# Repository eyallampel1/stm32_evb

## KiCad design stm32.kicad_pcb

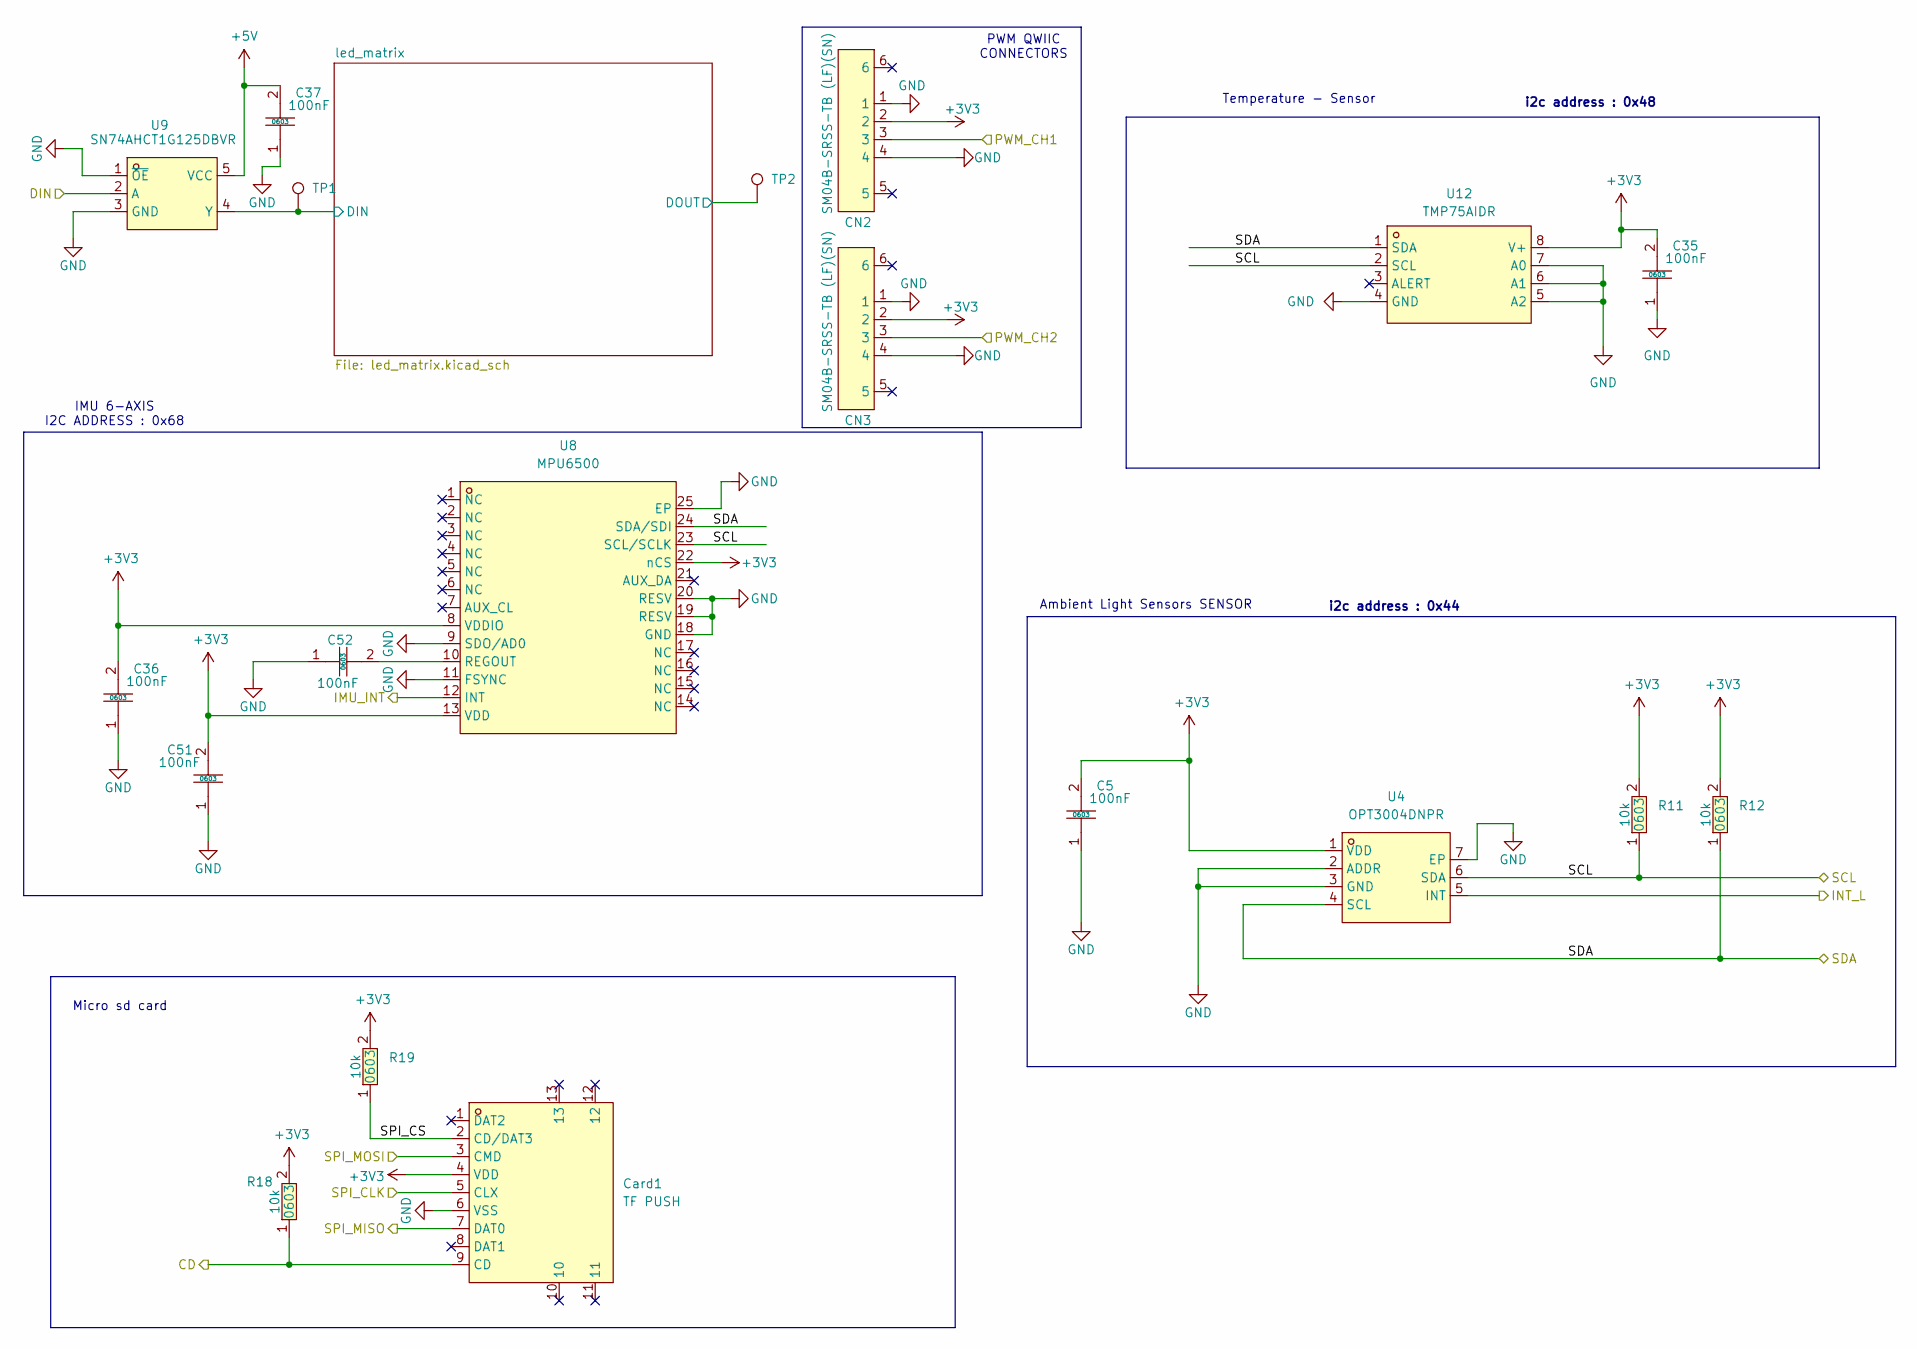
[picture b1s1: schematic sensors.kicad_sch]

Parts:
C5, C35, C36, C37, C51, C52: CC0603KRX7R9BB104; C0603; LCSC Part C14663
CN2, CN3: SM04B-SRSS-TB (LF)(SN); CONN-SMD_4P-P1.00_SM04B-SRSS-TB-LF-SN; LCSC Part C160404
Card1: TF PUSH; TF-SMD_TF-PUSH; LCSC Part C393941
R11, R12, R18, R19: 0603WAF1002T5E; R0603; LCSC Part C25804
TP1, TP2: TestPoint; TestPoint_Pad_2.0x2.0mm
U4: OPT3004DNPR; WSON-6_L2.0-W2.0-P0.65-TL-EP; LCSC Part C2655153
U8: MPU6500; QFN-24_L3.0-W3.0-P0.40-BL-EP; LCSC Part C50278
U9: SN74AHCT1G125DBVR; SOT-23-5_L3.0-W1.7-P0.95-LS2.8-BR; LCSC Part C7484
U12: TMP75AIDR; SOIC-8_L4.9-W3.9-P1.27-LS6.0-BL; LCSC Part C30389

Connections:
+3V3: C5.2, C35.2, C36.2, C51.2, CN2.2, CN3.2, Card1.4 (VDD), R11.2, R12.2, R18.2, R19.2, U4.1 (VDD), U8.8 (VDDIO), U8.13 (VDD), U8.22 (nCS), U12.8 (V+); also elsewhere on the board
+5V: C37.2, U9.5 (VCC); also elsewhere on the board
/sensors/SCL: R11.1, U4.6 (SDA), U8.23 (SCL/SCLK), U12.2 (SCL); also elsewhere on the board
/sensors/SDA: R12.1, U4.4 (SCL), U8.24 (SDA/SDI), U12.1 (SDA); also elsewhere on the board
/sensors/SPI_CS: Card1.2 (CD/DAT3), R19.1
/sensors/led_matrix/DIN: TP1.1, U9.4 (Y); also elsewhere on the board
/sensors/led_matrix/DOUT: TP2.1; also elsewhere on the board
/stm32_page/IMU_INT: U8.12 (INT); also elsewhere on the board
/stm32_page/PWM_CH1: CN2.3; also elsewhere on the board
/stm32_page/PWM_CH4: CN3.3; also elsewhere on the board
/stm32_page/RGB_LEDS: U9.2 (A); also elsewhere on the board
/stm32_page/SD_CD: Card1.9 (CD), R18.1; also elsewhere on the board
/stm32_page/SPI1_MISO: Card1.7 (DAT0); also elsewhere on the board
/stm32_page/SPI1_MOSI: Card1.3 (CMD); also elsewhere on the board
/stm32_page/SPI1_SCK: Card1.5 (CLX); also elsewhere on the board
/stm32_page/SYS_WKUP1: U4.5 (INT); also elsewhere on the board
GND: C5.1, C35.1, C36.1, C37.1, C51.1, C52.1, CN2.1, CN2.4, CN3.1, CN3.4, Card1.6 (VSS), U4.2 (ADDR), U4.3 (GND), U4.7 (EP), U8.9 (SDO/AD0), U8.11 (FSYNC), U8.18 (GND), U8.19 (RESV), U8.20 (RESV), U8.25 (EP), U9.1 (~OE), U9.3 (GND), U12.4 (GND), U12.5 (A2), U12.6 (A1), U12.7 (A0); also elsewhere on the board
unnamed: C52.2, U8.10 (REGOUT)

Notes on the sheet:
PWM QWIIC CONNECTORS
Temperature - Sensor
i2c address : 0x48
Ambient Light Sensors SENSOR
IMU 6-AXIS I2C ADDRESS : 0x68
i2c address : 0x44
Micro sd card

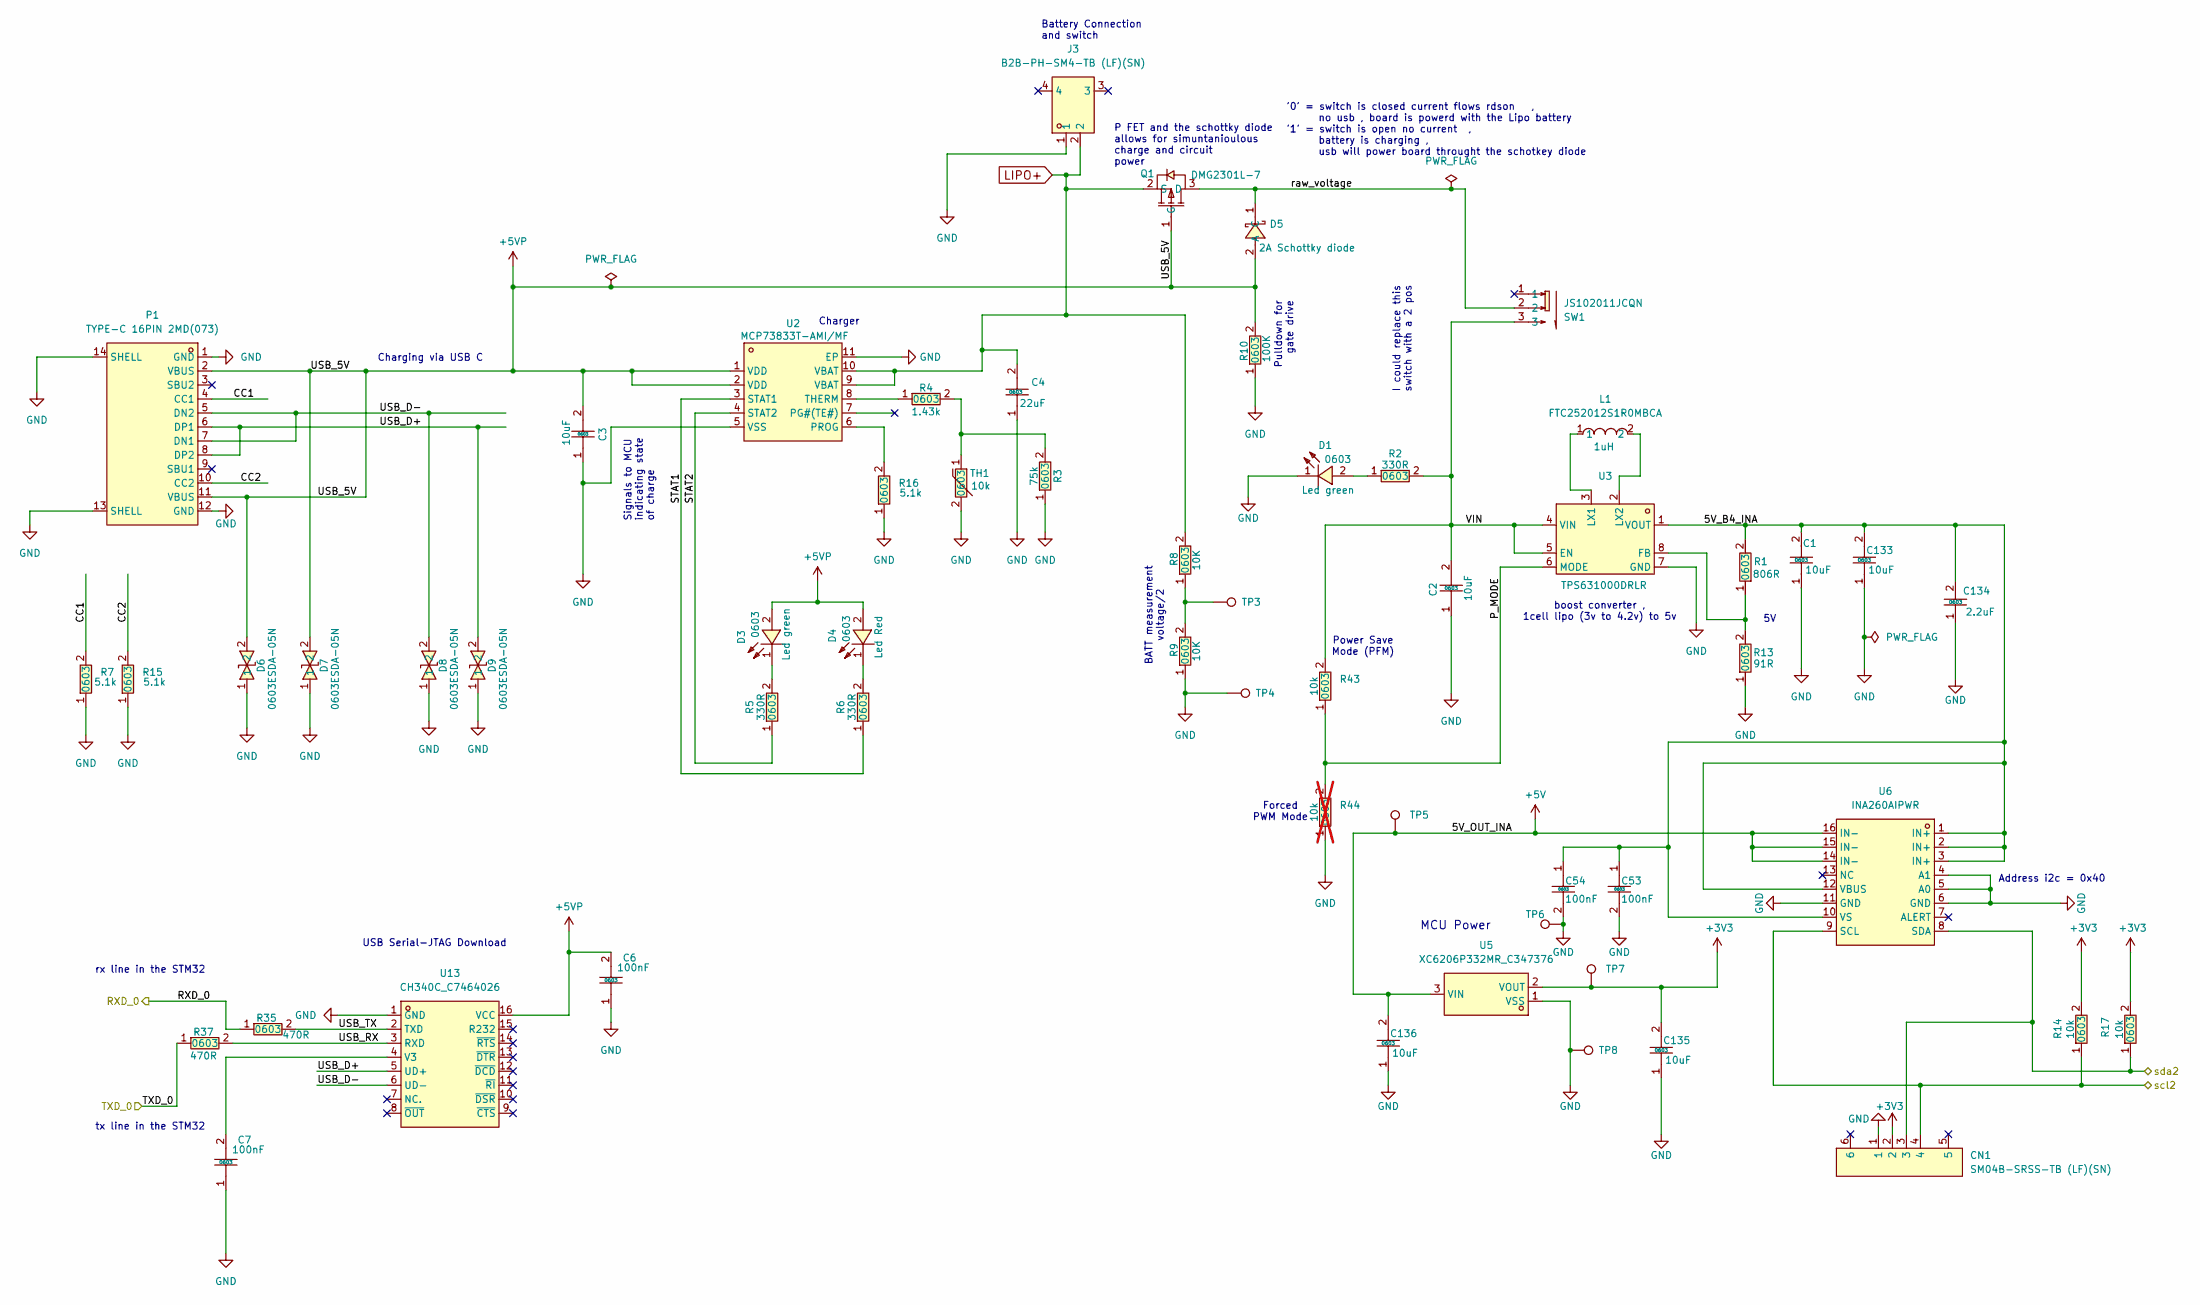
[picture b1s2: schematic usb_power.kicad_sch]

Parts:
C1, C2, C3, C133, C135, C136: CL10A106KP8NNNC; C0603; LCSC Part C19702
C4: CL10A226MP8NUNE; C0603; LCSC Part C86295
C6, C7, C53, C54: CC0603KRX7R9BB104; C0603; LCSC Part C14663
C134: CL10A225KO8NNNC; C0603; LCSC Part C23630
CN1: SM04B-SRSS-TB (LF)(SN); CONN-SMD_4P-P1.00_SM04B-SRSS-TB-LF-SN; LCSC Part C160404
D1, D3: 0603 Green 509-620mcd; LED0603-RD; LCSC Part C12624
D4: KT-0603R; LED0603-RD; LCSC Part C2286
D5: MBRA210LT3G_C5337989; SMA_L4.3-W2.6-LS5.1-RD; LCSC Part C5337989
D6, D7, D8, D9: 0603ESDA-05N; D0603-BI; LCSC Part C316054
J3: B2B-PH-SM4-TB (LF)(SN); CONN-SMD_B2B-PH-SM4-TB-LF-SN; LCSC Part C265003
L1: FTC252012S1R0MBCA; IND-SMD_L2.5-W2.0-VLS252012CX-150M; LCSC Part C5832370
P1: TYPE-C 16PIN 2MD(073); USB-C-SMD_TYPE-C-6PIN-2MD-073; LCSC Part C2765186
Q1: DMG2301L-7; SOT-23-3_L2.9-W1.3-P1.90-LS2.4-BR; LCSC Part C102619
R1: 0603WAF8060T5E; R0603; LCSC Part C23116
R2, R5, R6: 0603WAF3300T5E; R0603; LCSC Part C23138
R3: 0603WAF7502T5E; R0603; LCSC Part C23242
R4: 0603WAF1431T5E; R0603; LCSC Part C22840
R7, R15, R16: 0603WAF5101T5E; R0603; LCSC Part C23186
R8, R9, R14, R17, R43: 0603WAF1002T5E; R0603; LCSC Part C25804
R10: 0603WAF1003T5E; R0603; LCSC Part C25803
R13: 0603WAF910JT5E; R0603; LCSC Part C351621
R35, R37: 0603WAF4700T5E; R0603; LCSC Part C23179
R44: 0603WAF1002T5E; R0603; LCSC Part C25804; not fitted
SW1: JS102011JCQN; SW-SMD_JS102011JCQN; LCSC Part C221659
TH1: NCP18XH103F03RB; R0603; LCSC Part C13564
TP3, TP4, TP5, TP6, TP7, TP8: TestPoint; TestPoint_Pad_2.0x2.0mm
U2: MCP73833T-AMI/MF; DFN-10_L3.0-W3.0-P0.50-BL-EP-1; LCSC Part C340160
U3: TPS631000DRLR; SOT-583-8_L2.1-W1.2-P0.50-LS1.6-BL; LCSC Part C5219190
U5: XC6206P332MR_C347376; SOT-23-3_L3.0-W1.7-P0.95-LS2.9-BR; LCSC Part C347376
U6: INA260AIPWR; TSSOP-16_L5.0-W4.4-P0.65-LS6.4-BL-1; LCSC Part C2155885
U13: CH340C_C7464026; SOP-16_L10.0-W3.9-P1.27-LS6.0-BL; LCSC Part C7464026

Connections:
+3V3: C135.2, CN1.2, R14.2, R17.2, TP7.1, U5.2 (VOUT); also elsewhere on the board
+5V: C136.2, TP5.1, U5.3 (VIN), U6.14 (IN-), U6.15 (IN-), U6.16 (IN-); also elsewhere on the board
+5VP: C3.2, C6.2, D3.2 (A), D4.2 (A), D5.2 (A), D6.2, D7.2, P1.2 (VBUS), P1.11 (VBUS), Q1.1 (G), R10.2, U2.1 (VDD), U2.2 (VDD), U13.16 (VCC)
/USB/5V_B4_INA: C1.2, C53.1, C54.1, C133.2, C134.2, R1.2, U3.1 (VOUT), U6.1 (IN+), U6.2 (IN+), U6.3 (IN+), U6.10 (VS), U6.12 (VBUS)
/USB/CC1: P1.4 (CC1), R7.2
/USB/CC2: P1.10 (CC2), R15.2
/USB/P_MODE: R43.1, R44.2, U3.6 (MODE)
/USB/RXD_0: R35.1; also elsewhere on the board
/USB/STAT1: R6.1, U2.3 (STAT1)
/USB/STAT2: R5.1, U2.4 (STAT2)
/USB/TXD_0: R37.1; also elsewhere on the board
/USB/USB_D+: D9.2, P1.6 (DP1), P1.8 (DP2), U13.5 (UD+)
/USB/USB_D-: D8.2, P1.5 (DN2), P1.7 (DN1), U13.6 (UD-)
/USB/USB_RX: R37.2, U13.3 (RXD)
/USB/USB_TX: R35.2, U13.2 (TXD)
/USB/VIN: C2.2, R2.2, R43.2, SW1.3, U3.4 (VIN), U3.5 (EN)
/USB/raw_voltage: D5.1 (C), Q1.3 (D), SW1.2
/stm32_page/I2C3_SCL: CN1.4, R14.1, U6.9 (SCL); also elsewhere on the board
/stm32_page/I2C3_SDA: CN1.3, R17.1, U6.8 (SDA); also elsewhere on the board
GND: C1.1, C2.1, C3.1, C4.1, C6.1, C7.1, C53.2, C54.2, C133.1, C134.1, C135.1, C136.1, CN1.1, D1.1 (K), D6.1, D7.1, D8.1, D9.1, J3.1, P1.1 (GND), P1.12 (GND), P1.13 (SHELL), P1.14 (SHELL), R3.1, R7.1, R9.1, R10.1, R13.1, R15.1, R16.1, R44.1, TH1.2, TP4.1, TP6.1, TP8.1, U2.5 (VSS), U2.11 (EP), U3.7 (GND), U5.1 (VSS), U6.4 (A1), U6.5 (A0), U6.6 (GND), U6.11 (GND), U13.1 (GND); also elsewhere on the board
LIPO+: C4.2, J3.2, Q1.2 (S), R8.2, U2.9 (VBAT), U2.10 (VBAT)
unnamed: D1.2 (A), R2.1
unnamed: D3.1 (K), R5.2
unnamed: D4.1 (K), R6.2
unnamed: R3.2, R4.2, TH1.1
unnamed: R8.1, R9.2, TP3.1
unnamed: R16.2, U2.6 (PROG)
unnamed: R4.1, U2.8 (THERM)
unnamed: R1.1, R13.2, U3.8 (FB)
unnamed: L1.1, U3.3 (LX1)
unnamed: L1.2, U3.2 (LX2)
unnamed: C7.2, U13.4 (V3)

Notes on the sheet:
Charger
Forced PWM Mode
rx line in the STM32
P FET and the schottky diode allows for simuntanioulous charge and circuit power
Pulldown for gate drive
USB Serial-JTAG Download
'0' = switch is closed current flows rdson , no usb , board is powerd with the Lipo battery '1' = switch is open no current , battery is charging , usb will power board throught the schotkey diode
boost converter , 1cell lipo (3v to 4.2v) to 5v
BATT measurement voltage/2
Power Save Mode (PFM)
Battery Connection and switch
Address i2c = 0x40
tx line in the STM32
I could replace this switch with a 2 pos
Signals to MCU indicating state of charge
MCU Power
Charging via USB C

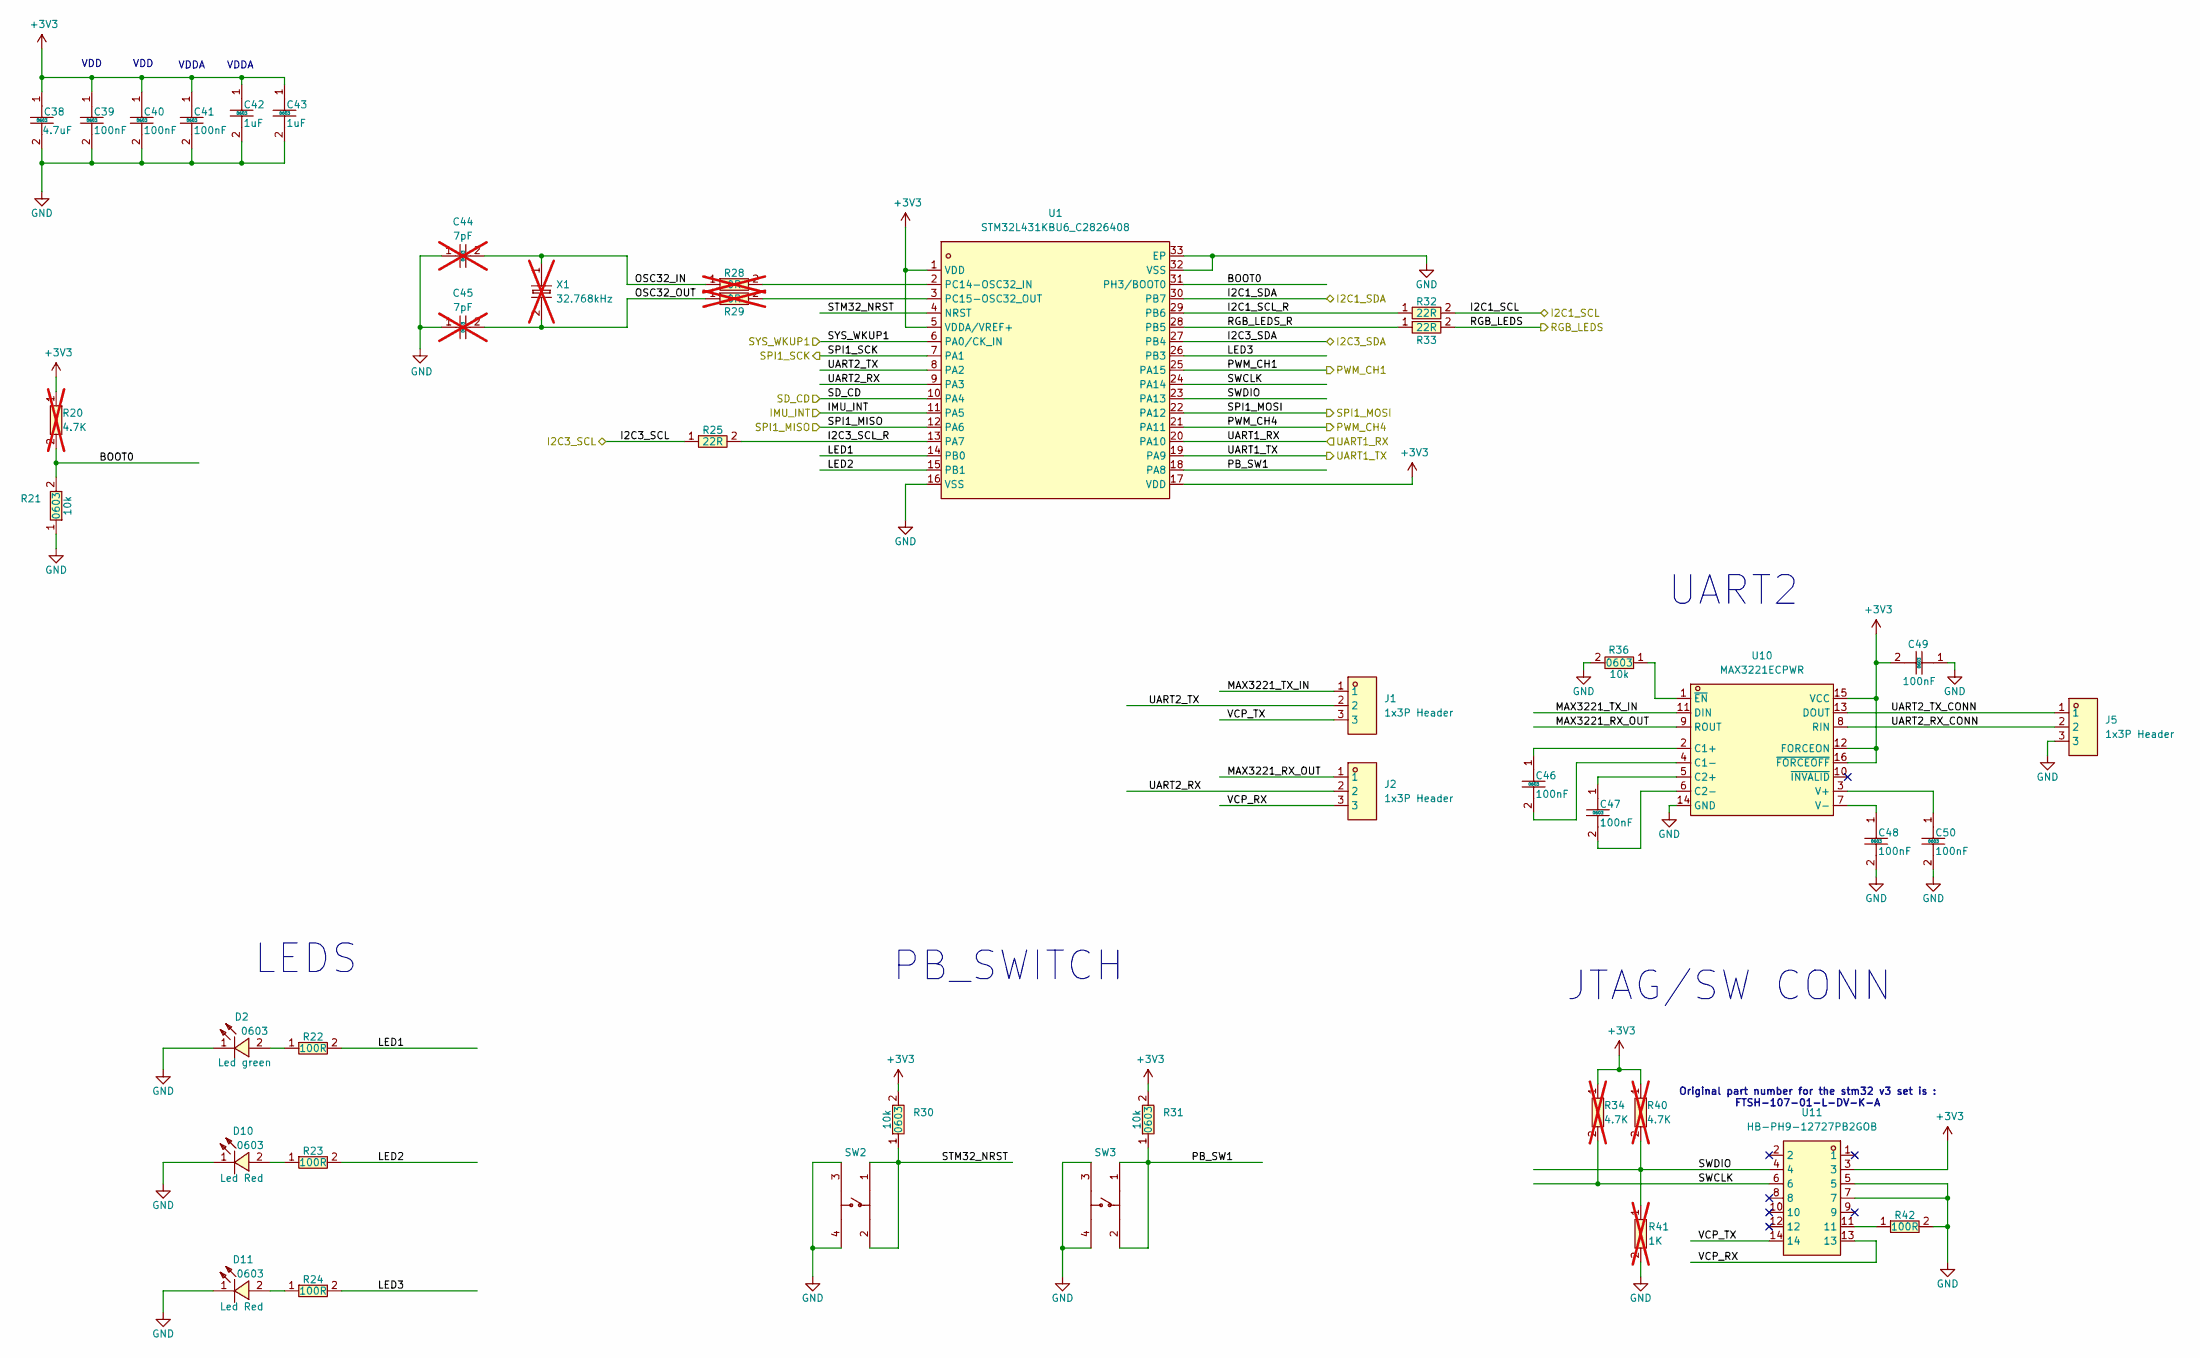
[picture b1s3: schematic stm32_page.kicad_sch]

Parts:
C38: CL10A475KO8NNNC; C0603; LCSC Part C19666
C39, C40, C41, C46, C47, C48, C49, C50: CC0603KRX7R9BB104; C0603; LCSC Part C14663
C42, C43: CL10A105KB8NNNC; C0603; LCSC Part C15849
C44, C45: 0603CG7R0C500NT; C0603; LCSC Part C1682; not fitted
D2: 0603 Green 509-620mcd; LED0603-RD; LCSC Part C12624
D10, D11: KT-0603R; LED0603-RD; LCSC Part C2286
J1, J2, J5: PZ254V-11-03P_C2937625; HDR-TH_3P-P2.54-V-M; LCSC Part C2937625
R20, R34, R40: 0603WAF4701T5E; R0603; LCSC Part C23162; not fitted
R21, R30, R31, R36: 0603WAF1002T5E; R0603; LCSC Part C25804
R22, R23, R24, R42: 0603WAF1000T5E; R0603; LCSC Part C22775
R25, R32, R33: 0603WAF220JT5E; R0603; LCSC Part C23345
R28, R29: 0603WAF0000T5E; R0603; LCSC Part C21189; not fitted
R41: 0603WAF1001T5E; R0603; LCSC Part C21190; not fitted
SW2, SW3: 6.0*6.0*6.0; SW-SMD_4P-L6.0-W6.0-P4.50-LS8.6; LCSC Part C5127964
U1: STM32L431KBU6_C2826408; QFN-32_L5.0-W5.0-P0.50-TL-EP3.5; LCSC Part C2826408
U10: MAX3221ECPWR; TSSOP-16_L5.0-W4.4-P0.65-LS6.4-BL; LCSC Part C350553
U11: HB-PH9-12727PB2GOB; HDR-SMD_14P-P1.27-V-M-R2-C7-LS5.5; LCSC Part C6332251
X1: SC-32S32.768kHz20PPM7pF; OSC-SMD_L3.2-W1.5; LCSC Part C97604; not fitted

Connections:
+3V3: C38.1, C39.1, C40.1, C41.1, C42.1, C43.1, C49.2, R20.1, R30.2, R31.2, R34.1, R40.1, U1.1 (VDD), U1.5 (VDDA/VREF+), U1.17 (VDD), U10.12 (FORCEON), U10.15 (VCC), U10.16 (~FORCEOFF), U11.3; also elsewhere on the board
/USB/RXD_0: U1.20 (PA10); also elsewhere on the board
/USB/TXD_0: U1.19 (PA9); also elsewhere on the board
/sensors/SCL: R32.2; also elsewhere on the board
/sensors/SDA: U1.30 (PB7); also elsewhere on the board
/stm32_page/BOOT0: R20.2, R21.2, U1.31 (PH3/BOOT0)
/stm32_page/I2C1_SCL_R: R32.1, U1.29 (PB6)
/stm32_page/I2C3_SCL: R25.1; also elsewhere on the board
/stm32_page/I2C3_SCL_R: R25.2, U1.13 (PA7)
/stm32_page/I2C3_SDA: U1.27 (PB4); also elsewhere on the board
/stm32_page/IMU_INT: U1.11 (PA5); also elsewhere on the board
/stm32_page/LED1: R22.2, U1.14 (PB0)
/stm32_page/LED2: R23.2, U1.15 (PB1)
/stm32_page/LED3: R24.2, U1.26 (PB3)
/stm32_page/MAX3221_RX_OUT: J2.1, U10.9 (ROUT)
/stm32_page/MAX3221_TX_IN: J1.1, U10.11 (DIN)
/stm32_page/OSC32_IN: C44.2, R28.1, X1.1
/stm32_page/OSC32_OUT: C45.2, R29.1, X1.2
/stm32_page/PB_SW1: R31.1, SW3.1, SW3.2, U1.18 (PA8)
/stm32_page/PWM_CH1: U1.25 (PA15); also elsewhere on the board
/stm32_page/PWM_CH4: U1.21 (PA11); also elsewhere on the board
/stm32_page/RGB_LEDS: R33.2; also elsewhere on the board
/stm32_page/RGB_LEDS_R: R33.1, U1.28 (PB5)
/stm32_page/SD_CD: U1.10 (PA4); also elsewhere on the board
/stm32_page/SPI1_MISO: U1.12 (PA6); also elsewhere on the board
/stm32_page/SPI1_MOSI: U1.22 (PA12); also elsewhere on the board
/stm32_page/SPI1_SCK: U1.7 (PA1); also elsewhere on the board
/stm32_page/STM32_NRST: R30.1, SW2.1, SW2.2, U1.4 (NRST)
/stm32_page/SWCLK: R34.2, U1.24 (PA14), U11.6
/stm32_page/SWDIO: R40.2, R41.1, U1.23 (PA13), U11.4
/stm32_page/SYS_WKUP1: U1.6 (PA0/CK_IN); also elsewhere on the board
/stm32_page/UART2_RX: J2.2, U1.9 (PA3)
/stm32_page/UART2_RX_CONN: J5.2, U10.8 (RIN)
/stm32_page/UART2_TX: J1.2, U1.8 (PA2)
/stm32_page/UART2_TX_CONN: J5.1, U10.13 (DOUT)
/stm32_page/VCP_RX: J2.3, U11.13
/stm32_page/VCP_TX: J1.3, U11.14
GND: C38.2, C39.2, C40.2, C41.2, C42.2, C43.2, C44.1, C45.1, C48.2, C49.1, C50.2, D2.1 (K), D10.1 (K), D11.1 (K), J5.3, R21.1, R36.2, R41.2, R42.2, SW2.3, SW2.4, SW3.3, SW3.4, U1.16 (VSS), U1.32 (VSS), U1.33 (EP), U10.14 (GND), U11.5, U11.7; also elsewhere on the board
unnamed: D2.2 (A), R22.1
unnamed: D10.2 (A), R23.1
unnamed: D11.2 (A), R24.1
unnamed: R42.1, U11.11
unnamed: R28.2, U1.2 (PC14-OSC32_IN)
unnamed: R29.2, U1.3 (PC15-OSC32_OUT)
unnamed: C46.1, U10.2 (C1+)
unnamed: C46.2, U10.4 (C1-)
unnamed: C47.1, U10.5 (C2+)
unnamed: C47.2, U10.6 (C2-)
unnamed: C50.1, U10.3 (V+)
unnamed: C48.1, U10.7 (V-)
unnamed: R36.1, U10.1 (~EN)

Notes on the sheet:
PB_SWITCH
LEDS
VDD
JTAG/SW CONN
VDDA
Original part number for the stm32 v3 set is : FTSH-107-01-L-DV-K-A
UART2

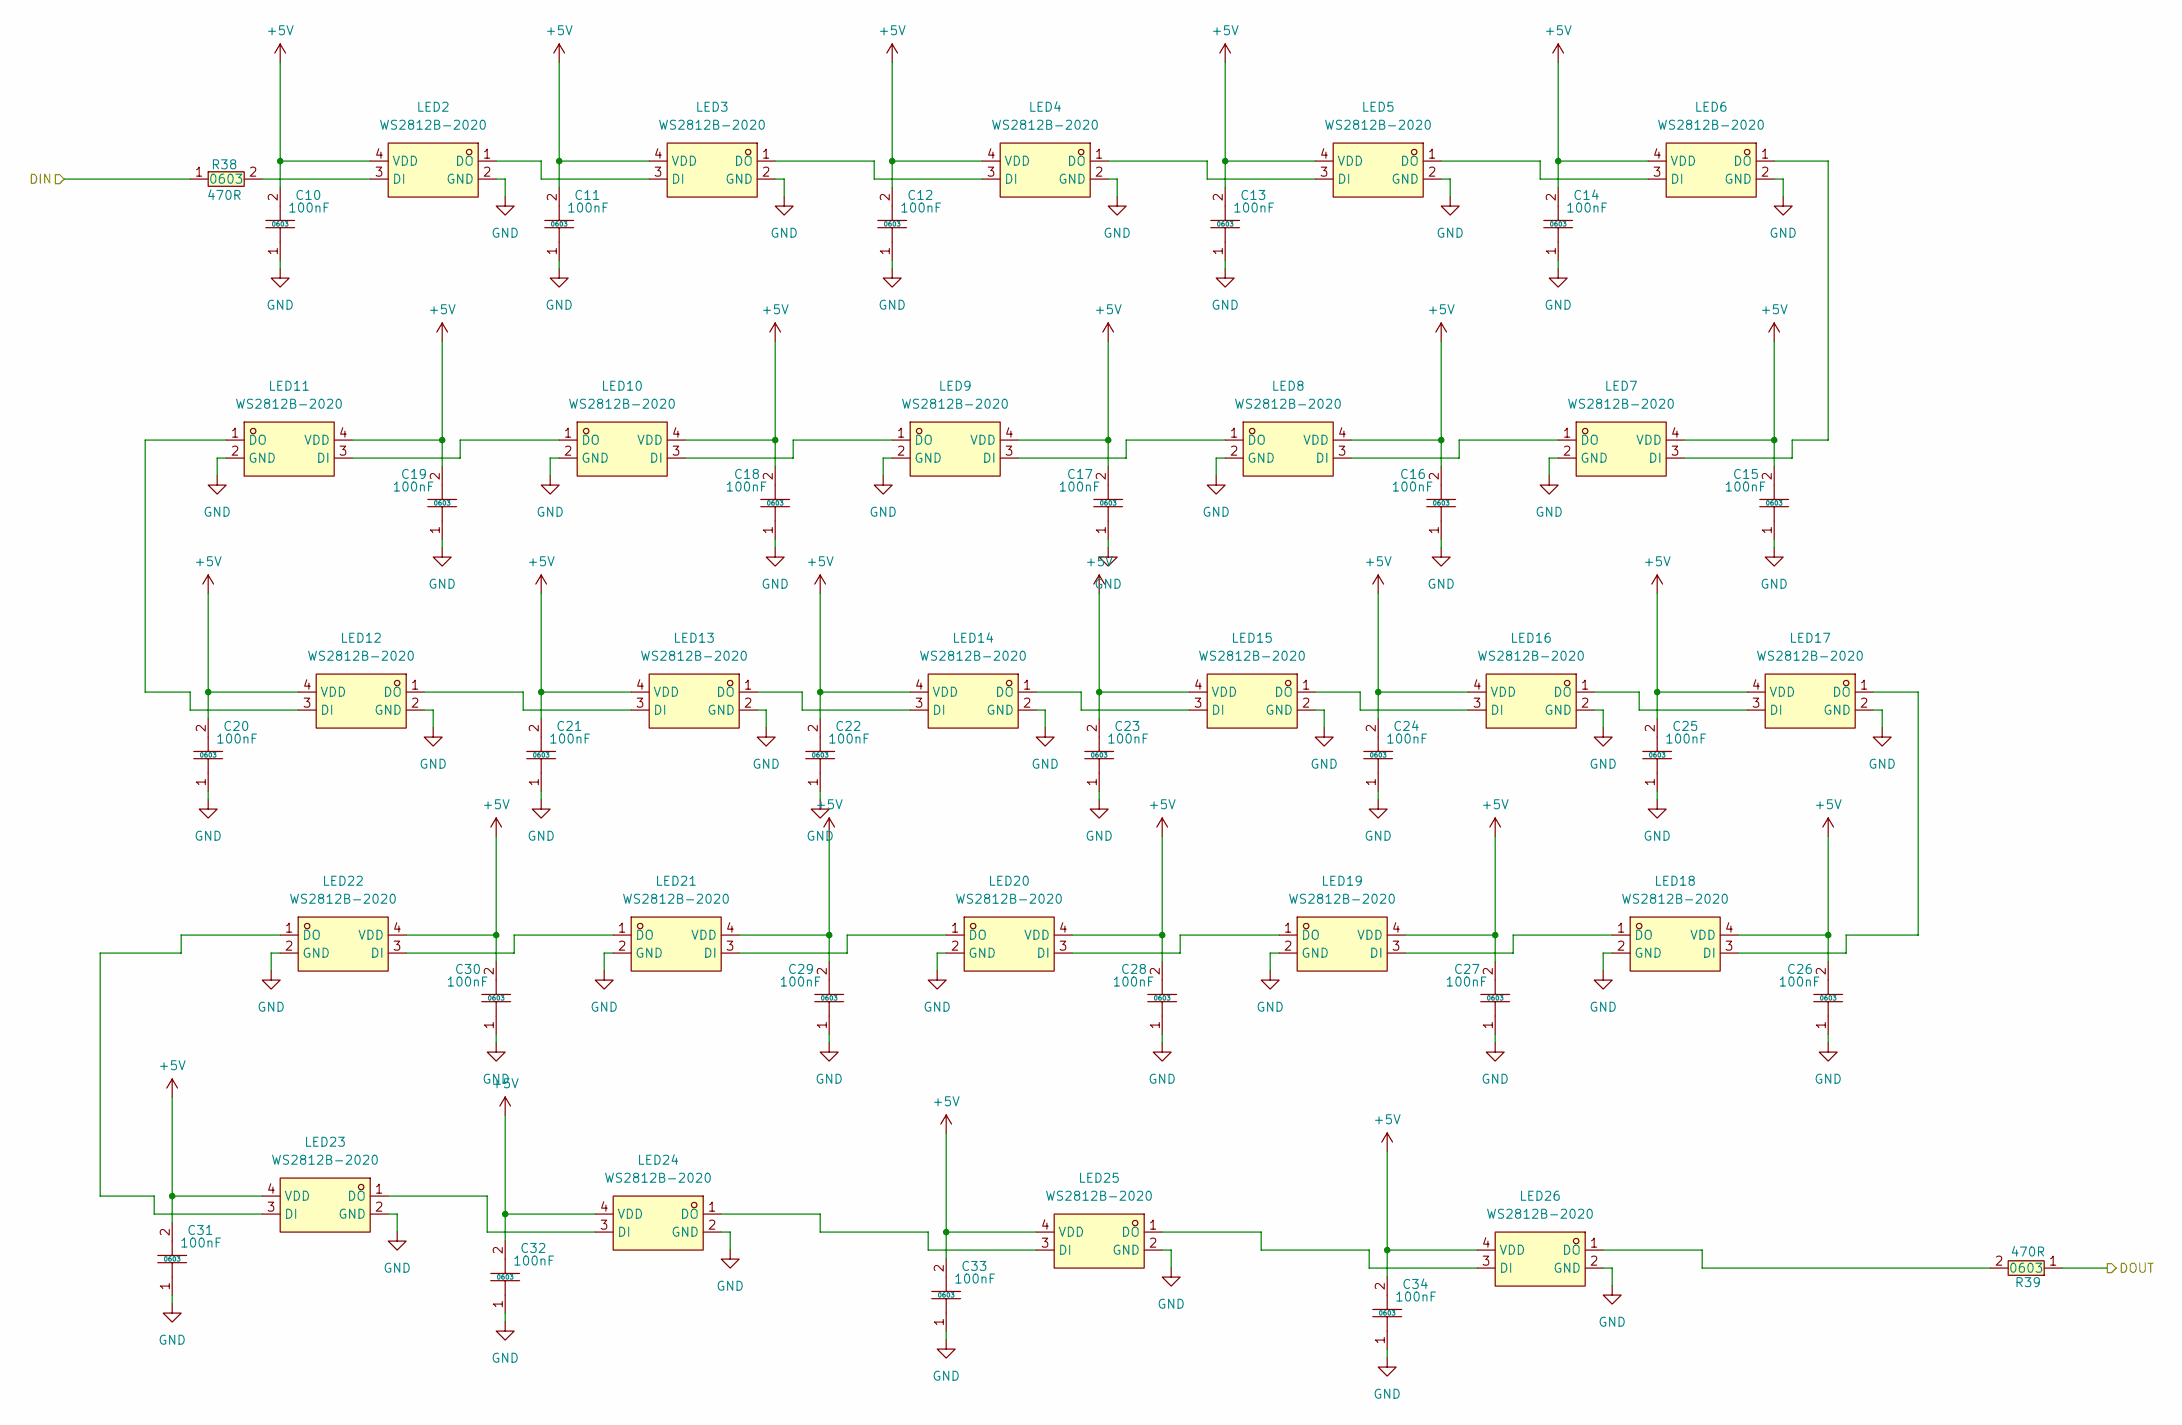
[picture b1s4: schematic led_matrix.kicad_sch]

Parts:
C10, C11, C12, C13, C14, C15, C16, C17, C18, C19, C20, C21, C22, C23, C24, C25, C26, C27, C28, C29, C30, C31, C32, C33, C34: CC0603KRX7R9BB104; C0603; LCSC Part C14663
LED2, LED3, LED4, LED5, LED6, LED7, LED8, LED9, LED10, LED11, LED12, LED13, LED14, LED15, LED16, LED17, LED18, LED19, LED20, LED21, LED22, LED23, LED24, LED25, LED26: WS2812B-2020; LED-SMD_4P-L2.0-W2.0-TL_WS2812B-2020; LCSC Part C965555
R38, R39: 0603WAF4700T5E; R0603; LCSC Part C23179

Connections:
+5V: C10.2, C11.2, C12.2, C13.2, C14.2, C15.2, C16.2, C17.2, C18.2, C19.2, C20.2, C21.2, C22.2, C23.2, C24.2, C25.2, C26.2, C27.2, C28.2, C29.2, C30.2, C31.2, C32.2, C33.2, C34.2, LED2.4 (VDD), LED3.4 (VDD), LED4.4 (VDD), LED5.4 (VDD), LED6.4 (VDD), LED7.4 (VDD), LED8.4 (VDD), LED9.4 (VDD), LED10.4 (VDD), LED11.4 (VDD), LED12.4 (VDD), LED13.4 (VDD), LED14.4 (VDD), LED15.4 (VDD), LED16.4 (VDD), LED17.4 (VDD), LED18.4 (VDD), LED19.4 (VDD), LED20.4 (VDD), LED21.4 (VDD), LED22.4 (VDD), LED23.4 (VDD), LED24.4 (VDD), LED25.4 (VDD), LED26.4 (VDD); also elsewhere on the board
/sensors/led_matrix/DIN: R38.1; also elsewhere on the board
/sensors/led_matrix/DOUT: R39.1; also elsewhere on the board
GND: C10.1, C11.1, C12.1, C13.1, C14.1, C15.1, C16.1, C17.1, C18.1, C19.1, C20.1, C21.1, C22.1, C23.1, C24.1, C25.1, C26.1, C27.1, C28.1, C29.1, C30.1, C31.1, C32.1, C33.1, C34.1, LED2.2 (GND), LED3.2 (GND), LED4.2 (GND), LED5.2 (GND), LED6.2 (GND), LED7.2 (GND), LED8.2 (GND), LED9.2 (GND), LED10.2 (GND), LED11.2 (GND), LED12.2 (GND), LED13.2 (GND), LED14.2 (GND), LED15.2 (GND), LED16.2 (GND), LED17.2 (GND), LED18.2 (GND), LED19.2 (GND), LED20.2 (GND), LED21.2 (GND), LED22.2 (GND), LED23.2 (GND), LED24.2 (GND), LED25.2 (GND), LED26.2 (GND); also elsewhere on the board
unnamed: LED2.3 (DI), R38.2
unnamed: LED2.1 (DO), LED3.3 (DI)
unnamed: LED3.1 (DO), LED4.3 (DI)
unnamed: LED4.1 (DO), LED5.3 (DI)
unnamed: LED5.1 (DO), LED6.3 (DI)
unnamed: LED6.1 (DO), LED7.3 (DI)
unnamed: LED7.1 (DO), LED8.3 (DI)
unnamed: LED8.1 (DO), LED9.3 (DI)
unnamed: LED9.1 (DO), LED10.3 (DI)
unnamed: LED10.1 (DO), LED11.3 (DI)
unnamed: LED11.1 (DO), LED12.3 (DI)
unnamed: LED12.1 (DO), LED13.3 (DI)
unnamed: LED13.1 (DO), LED14.3 (DI)
unnamed: LED14.1 (DO), LED15.3 (DI)
unnamed: LED15.1 (DO), LED16.3 (DI)
unnamed: LED16.1 (DO), LED17.3 (DI)
unnamed: LED17.1 (DO), LED18.3 (DI)
unnamed: LED18.1 (DO), LED19.3 (DI)
unnamed: LED19.1 (DO), LED20.3 (DI)
unnamed: LED20.1 (DO), LED21.3 (DI)
unnamed: LED21.1 (DO), LED22.3 (DI)
unnamed: LED22.1 (DO), LED23.3 (DI)
unnamed: LED23.1 (DO), LED24.3 (DI)
unnamed: LED24.1 (DO), LED25.3 (DI)
unnamed: LED25.1 (DO), LED26.3 (DI)
unnamed: LED26.1 (DO), R39.2

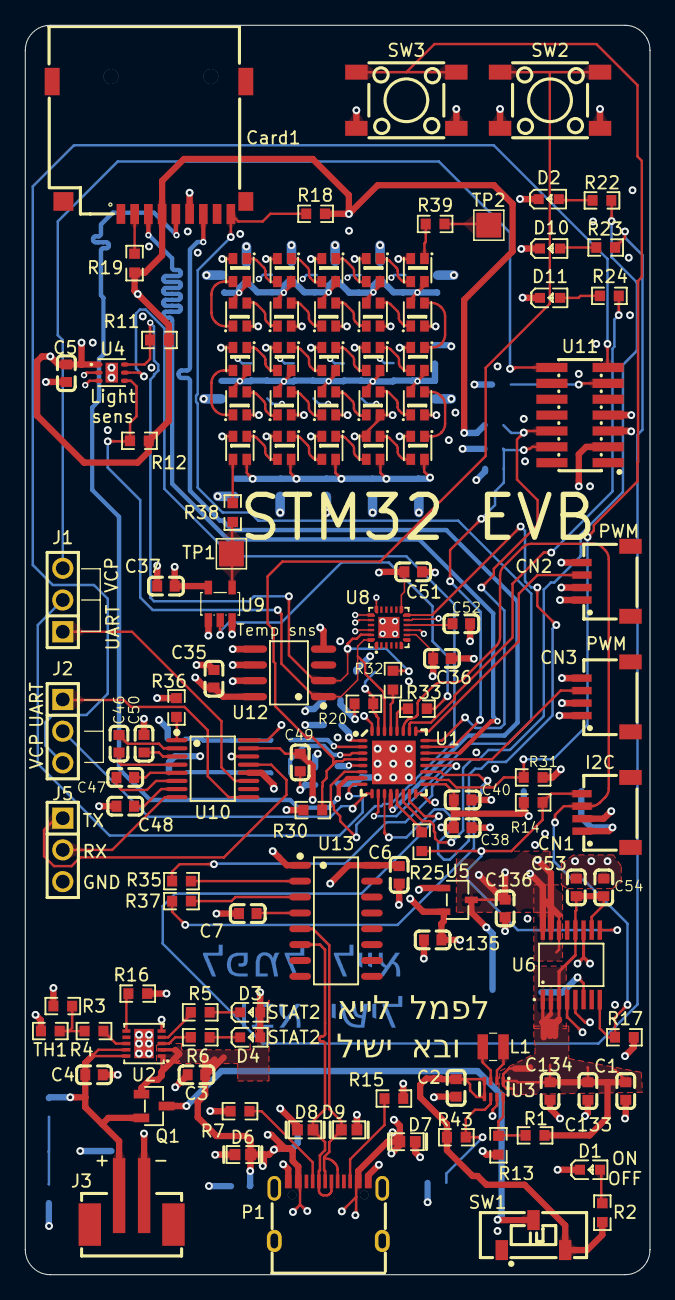
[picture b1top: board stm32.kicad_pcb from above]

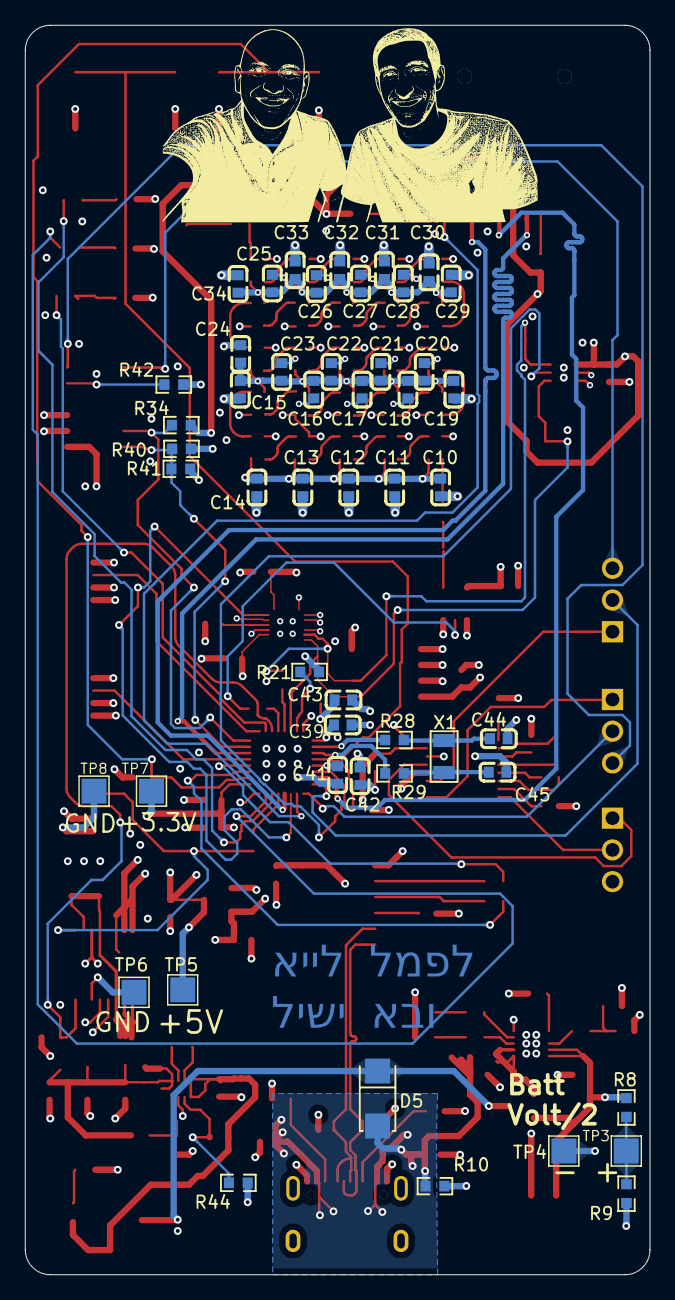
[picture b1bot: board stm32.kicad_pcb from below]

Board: 4 copper layers, 50.0 x 100.0 mm, 170 parts (50 on the bottom side), 107 nets.

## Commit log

2025-03-25 test lishau
2025-03-26 Added usb block - still need to check
2025-03-26 adding jtag and power cap
2025-03-26 Added some sensors and ch340
2025-03-27 updating res and cap to 0603, adding OSC32 DRP, JTAG done, power done
2025-03-27 Added some sensors and current sensor
2025-03-28 Added led matrix and ina260
2025-03-30 Cap updated again to basic parts
2025-03-30 Add IO pinout - 2 I2C, 2UART, 1 SPI, LEDs, switches,2 interupts,RST
2025-03-30 Add LEDs,22r to I2C, UART conv, power conn, remove JTAG to SW debug
2025-03-30 Finished sensor / usb block
2025-03-30 add SD_CD, PB_SW for NRST, 22R for RGB, 1X3 headers for uart and VCP option, block ports
2025-03-30 Add PWM and LED. After this commit I will connect the TOP
2025-03-30 Finished schematic need to check , before layout
2025-03-31 replaced part for lower cost
2025-04-02 Changed lga sensors to cheap qfn soic8 package
2025-04-02 removed 1uf cap
2025-04-02 Changed a bit component that where out of stock
2025-04-03 Added some no connect flag
2025-04-03 Added pull up / pull down on mode pin tps
2025-04-03 Added missing filter caps on ina260
2025-04-03 Removed VBAT wrong text on stm32 page
2025-04-04 Advanced placement , minor schem changes
2025-04-05 Finished placement , added few TP's
2025-04-05 WIP routing still not finished
2025-04-05 Finished routing
2025-04-06 Swap L4 with L3 and finished routing
2025-04-06 Working on drc in pcb
2025-04-06 Fixed some drc errors
2025-04-06 Finished board ,now to production
2025-04-07 imporve some nets
2025-04-07 length match some lines
